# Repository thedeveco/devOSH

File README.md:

# The DevEco Open Hardware Initiative

This repository serves as a central location for open hardware collaboration that is inspired the by devEco.

The hope is create a flourishing hardware ecosystem that the community can rally around, learn from and adapt to create new exciting projects.

## Live stream
- [Live stream informaton](LIVESTREAM.md)

## Directories

### Projects
- [B3VY LED badge](https://github.com/mwelling/b3vy_led)
- [FPV Omnibot](https://github.com/HeavyFalcon678/FPV-Omnibot)
- [Electronic Makerchip](https://github.com/thedeveco/maker-chip-standard)

#### Current Projects
- [ECP-V Wireless](https://github.com/mwelling/ECP-V-Wireless)

### Studies

### Tutorials

## Administrators

### Michael Welling (Discord m_w)

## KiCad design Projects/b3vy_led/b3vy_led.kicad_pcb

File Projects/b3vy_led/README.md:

## B3VY LED badge

A badge design in the shape of the B3VY logo. Created to help promote the B3VY network at Open Sauce Conference 2025.

### Specifications
- ESP32-S3 mini module
- 8x6 grid of programmable RGB LEDs
- USB C connector for power and programming

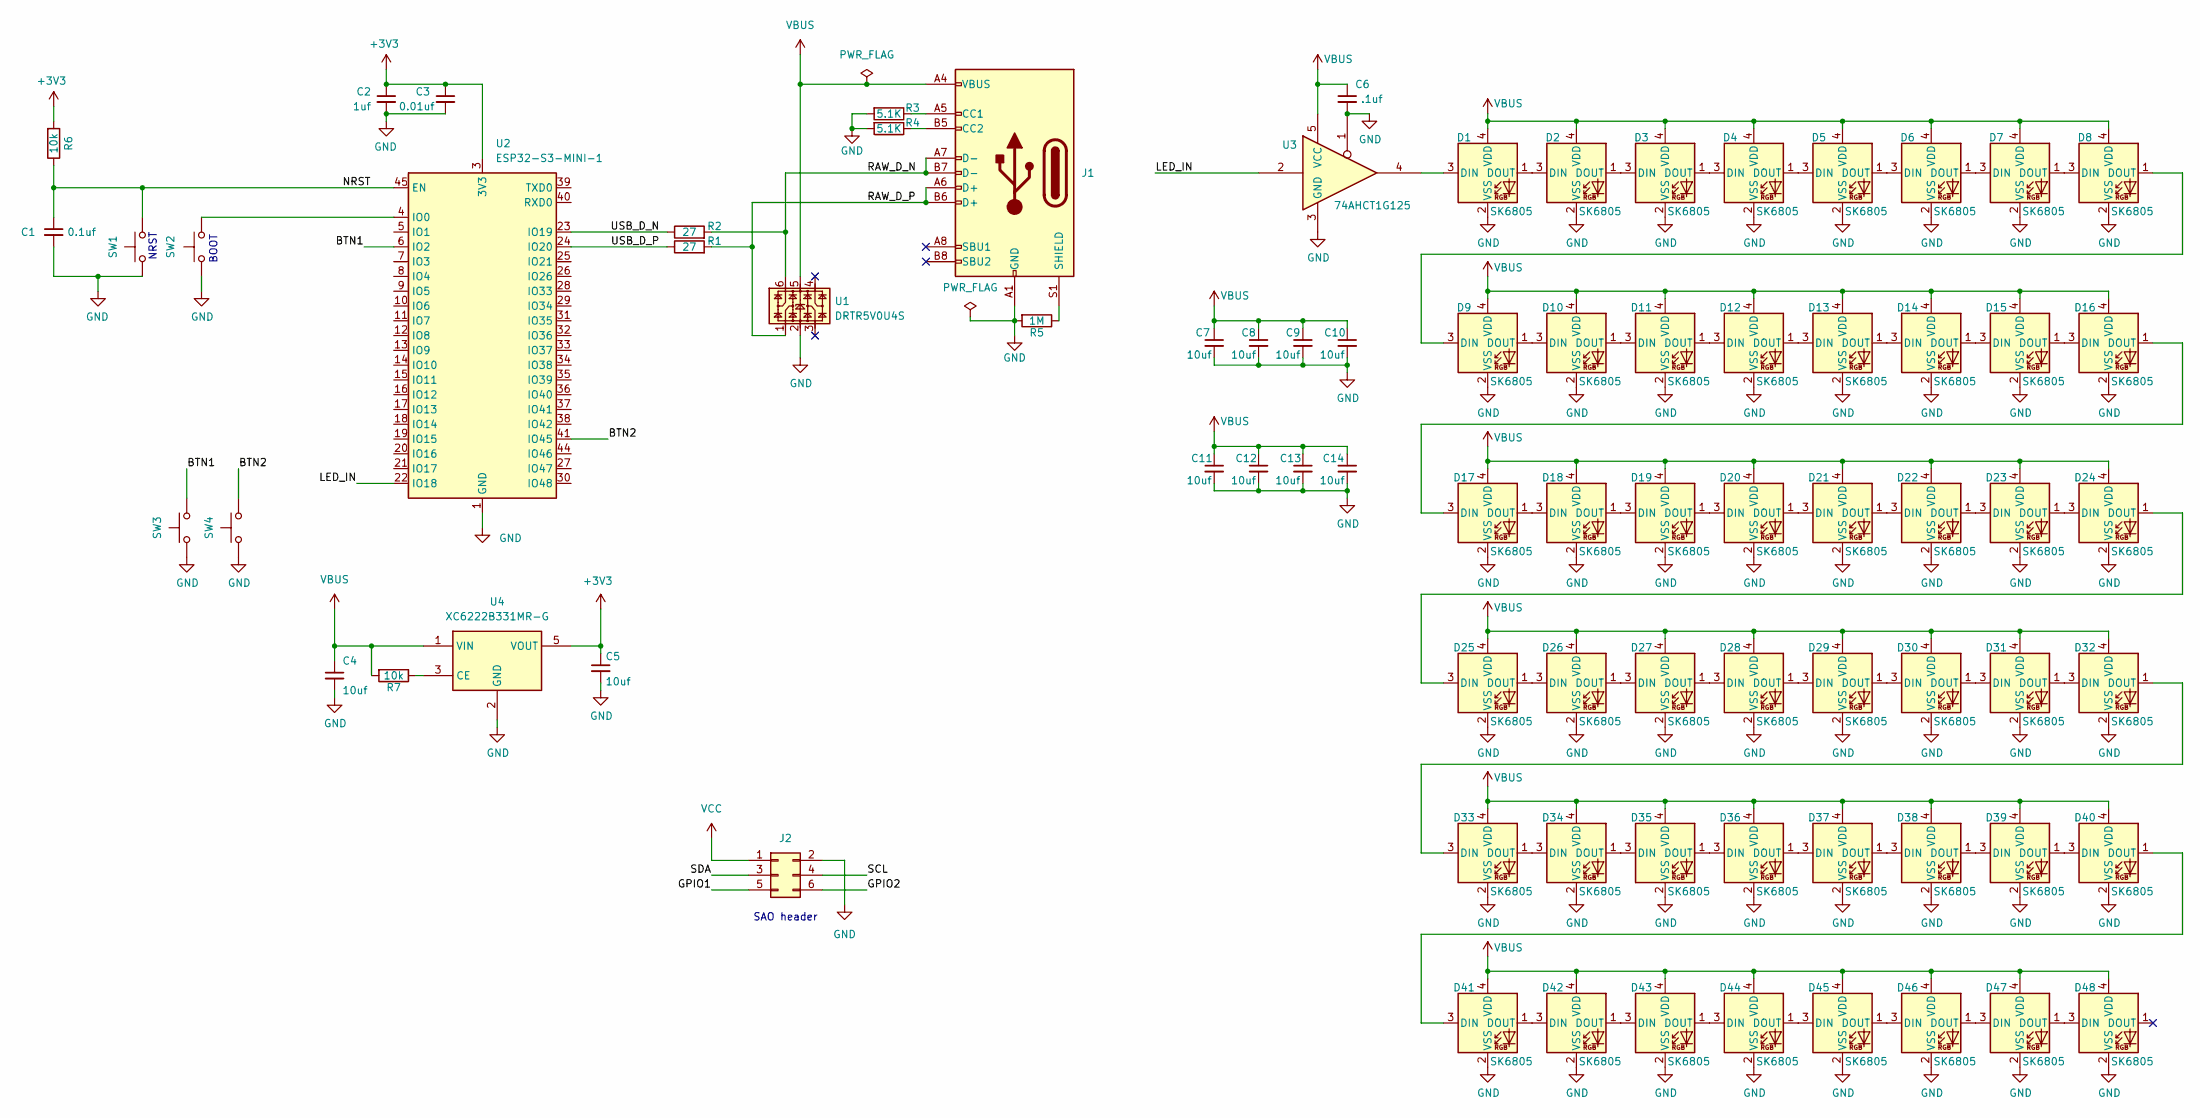
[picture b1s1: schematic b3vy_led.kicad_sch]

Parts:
C1: 0.1uf; C_0402_1005Metric
C2: 1uf; C_0603_1608Metric
C3: 0.01uf; C_0603_1608Metric
C4, C5, C7, C8, C9, C10, C11, C12, C13, C14: 10uf; C_0805_2012Metric
C6: .1uf; C_0603_1608Metric
D1, D2, D3, D4, D5, D6, D7, D8, D9, D10, D11, D12, D13, D14, D15, D16, D17, D18, D19, D20, D21, D22, D23, D24, D25, D26, D27, D28, D29, D30, D31, D32, D33, D34, D35, D36, D37, D38, D39, D40, D41, D42, D43, D44, D45, D46, D47, D48: SK6805; LED_SK6805_PLCC4_2.4x2.7mm_P1.3mm
J1: USB_C_Receptacle_USB2.0; USB_C_Receptacle_HRO_TYPE-C-31-M-12
J2: Conn_02x03_Odd_Even; PinHeader_2x03_P2.54mm_Vertical
R1, R2: 27; R_0402_1005Metric
R3, R4: 5.1K; R_0603_1608Metric
R5: 1M; R_0603_1608Metric
R6, R7: 10k; R_0603_1608Metric
SW1, SW2, SW3, SW4: SW_Push; SW_SPST_PTS810
U1: DRTR5V0U4S; SOT-363_SC-70-6
U2: ESP32-S3-MINI-1; ESP32-S2-MINI-1
U3: 74AHCT1G125; SOT-23-5
U4: XC6222B331MR-G; SOT-23-5

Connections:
+3V3: C2.1, C3.1, C5.1, R6.2, U2.3 (3V3), U4.5 (VOUT)
/BTN1: SW3.2, U2.6 (IO2)
/BTN2: SW4.2, U2.41 (IO45)
/GPIO1: J2.5
/GPIO2: J2.6
/LED_IN: U2.22 (IO18), U3.2
/NRST: C1.1, R6.1, SW1.2, U2.45 (EN)
/RAW_D_N: J1.A7 (D-), J1.B7 (D-), R2.2, U1.6
/RAW_D_P: J1.A6 (D+), J1.B6 (D+), R1.2, U1.1
/SCL: J2.4
/SDA: J2.3
/USB_D_N: R2.1, U2.23 (IO19)
/USB_D_P: R1.1, U2.24 (IO20)
GND: C1.2, C2.2, C3.2, C4.2, C5.2, C6.2, C7.2, C8.2, C9.2, C10.2, C11.2, C12.2, C13.2, C14.2, D1.2 (VSS), D2.2 (VSS), D3.2 (VSS), D4.2 (VSS), D5.2 (VSS), D6.2 (VSS), D7.2 (VSS), D8.2 (VSS), D9.2 (VSS), D10.2 (VSS), D11.2 (VSS), D12.2 (VSS), D13.2 (VSS), D14.2 (VSS), D15.2 (VSS), D16.2 (VSS), D17.2 (VSS), D18.2 (VSS), D19.2 (VSS), D20.2 (VSS), D21.2 (VSS), D22.2 (VSS), D23.2 (VSS), D24.2 (VSS), D25.2 (VSS), D26.2 (VSS), D27.2 (VSS), D28.2 (VSS), D29.2 (VSS), D30.2 (VSS), D31.2 (VSS), D32.2 (VSS), D33.2 (VSS), D34.2 (VSS), D35.2 (VSS), D36.2 (VSS), D37.2 (VSS), D38.2 (VSS), D39.2 (VSS), D40.2 (VSS), D41.2 (VSS), D42.2 (VSS), D43.2 (VSS), D44.2 (VSS), D45.2 (VSS), D46.2 (VSS), D47.2 (VSS), D48.2 (VSS), J1.A1 (GND), J1.A12 (GND), J1.B1 (GND), J1.B12 (GND), J2.2, R3.2, R4.2, R5.2, SW1.1, SW2.1, SW3.1, SW4.1, U1.2, U2.1 (GND), U2.2 (GND), U2.42 (GND), U2.43 (GND), U2.46 (GND), U2.47 (GND), U2.48 (GND), U2.49 (GND), U2.50 (GND), U2.51 (GND), U2.52 (GND), U2.53 (GND), U2.54 (GND), U2.55 (GND), U2.56 (GND), U2.57 (GND), U2.58 (GND), U2.59 (GND), U2.60 (GND), U2.61 (GND), U2.62 (GND), U2.63 (GND), U2.64 (GND), U2.65 (GND), U3.1, U3.3 (GND), U4.2 (GND)
unnamed: D1.3 (DIN), U3.4
unnamed: D1.1 (DOUT), D2.3 (DIN)
unnamed: D2.1 (DOUT), D3.3 (DIN)
unnamed: D3.1 (DOUT), D4.3 (DIN)
unnamed: D4.1 (DOUT), D5.3 (DIN)
unnamed: D5.1 (DOUT), D6.3 (DIN)
unnamed: D6.1 (DOUT), D7.3 (DIN)
unnamed: D7.1 (DOUT), D8.3 (DIN)
unnamed: D8.1 (DOUT), D9.3 (DIN)
unnamed: D9.1 (DOUT), D10.3 (DIN)
unnamed: D10.1 (DOUT), D11.3 (DIN)
unnamed: D11.1 (DOUT), D12.3 (DIN)
unnamed: D12.1 (DOUT), D13.3 (DIN)
unnamed: D13.1 (DOUT), D14.3 (DIN)
unnamed: D14.1 (DOUT), D15.3 (DIN)
unnamed: D15.1 (DOUT), D16.3 (DIN)
unnamed: D16.1 (DOUT), D17.3 (DIN)
unnamed: D17.1 (DOUT), D18.3 (DIN)
unnamed: D18.1 (DOUT), D19.3 (DIN)
unnamed: D19.1 (DOUT), D20.3 (DIN)
unnamed: D20.1 (DOUT), D21.3 (DIN)
unnamed: D21.1 (DOUT), D22.3 (DIN)
unnamed: D22.1 (DOUT), D23.3 (DIN)
unnamed: D23.1 (DOUT), D24.3 (DIN)
unnamed: D24.1 (DOUT), D25.3 (DIN)
unnamed: D25.1 (DOUT), D26.3 (DIN)
unnamed: D26.1 (DOUT), D27.3 (DIN)
unnamed: D27.1 (DOUT), D28.3 (DIN)
unnamed: D28.1 (DOUT), D29.3 (DIN)
unnamed: D29.1 (DOUT), D30.3 (DIN)
unnamed: D30.1 (DOUT), D31.3 (DIN)
unnamed: D31.1 (DOUT), D32.3 (DIN)
unnamed: D32.1 (DOUT), D33.3 (DIN)
unnamed: D33.1 (DOUT), D34.3 (DIN)
unnamed: D34.1 (DOUT), D35.3 (DIN)
unnamed: D35.1 (DOUT), D36.3 (DIN)
unnamed: D36.1 (DOUT), D37.3 (DIN)
unnamed: D37.1 (DOUT), D38.3 (DIN)
unnamed: D38.1 (DOUT), D39.3 (DIN)
unnamed: D39.1 (DOUT), D40.3 (DIN)
unnamed: D40.1 (DOUT), D41.3 (DIN)
unnamed: D41.1 (DOUT), D42.3 (DIN)
unnamed: D42.1 (DOUT), D43.3 (DIN)
unnamed: D43.1 (DOUT), D44.3 (DIN)
unnamed: D44.1 (DOUT), D45.3 (DIN)
unnamed: D45.1 (DOUT), D46.3 (DIN)
unnamed: D46.1 (DOUT), D47.3 (DIN)
unnamed: D47.1 (DOUT), D48.3 (DIN)
unnamed: J1.A5 (CC1), R3.1
unnamed: J1.B5 (CC2), R4.1
unnamed: J1.S1 (SHIELD), R5.1
unnamed: SW2.2, U2.4 (IO0)
unnamed: R7.1, U4.3 (CE)
VBUS: C4.1, C6.1, C7.1, C8.1, C9.1, C10.1, C11.1, C12.1, C13.1, C14.1, D1.4 (VDD), D2.4 (VDD), D3.4 (VDD), D4.4 (VDD), D5.4 (VDD), D6.4 (VDD), D7.4 (VDD), D8.4 (VDD), D9.4 (VDD), D10.4 (VDD), D11.4 (VDD), D12.4 (VDD), D13.4 (VDD), D14.4 (VDD), D15.4 (VDD), D16.4 (VDD), D17.4 (VDD), D18.4 (VDD), D19.4 (VDD), D20.4 (VDD), D21.4 (VDD), D22.4 (VDD), D23.4 (VDD), D24.4 (VDD), D25.4 (VDD), D26.4 (VDD), D27.4 (VDD), D28.4 (VDD), D29.4 (VDD), D30.4 (VDD), D31.4 (VDD), D32.4 (VDD), D33.4 (VDD), D34.4 (VDD), D35.4 (VDD), D36.4 (VDD), D37.4 (VDD), D38.4 (VDD), D39.4 (VDD), D40.4 (VDD), D41.4 (VDD), D42.4 (VDD), D43.4 (VDD), D44.4 (VDD), D45.4 (VDD), D46.4 (VDD), D47.4 (VDD), D48.4 (VDD), J1.A4 (VBUS), J1.A9 (VBUS), J1.B4 (VBUS), J1.B9 (VBUS), R7.2, U1.5, U3.5 (VCC), U4.1 (VIN)
VCC: J2.1

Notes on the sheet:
NRST
BOOT
SAO header

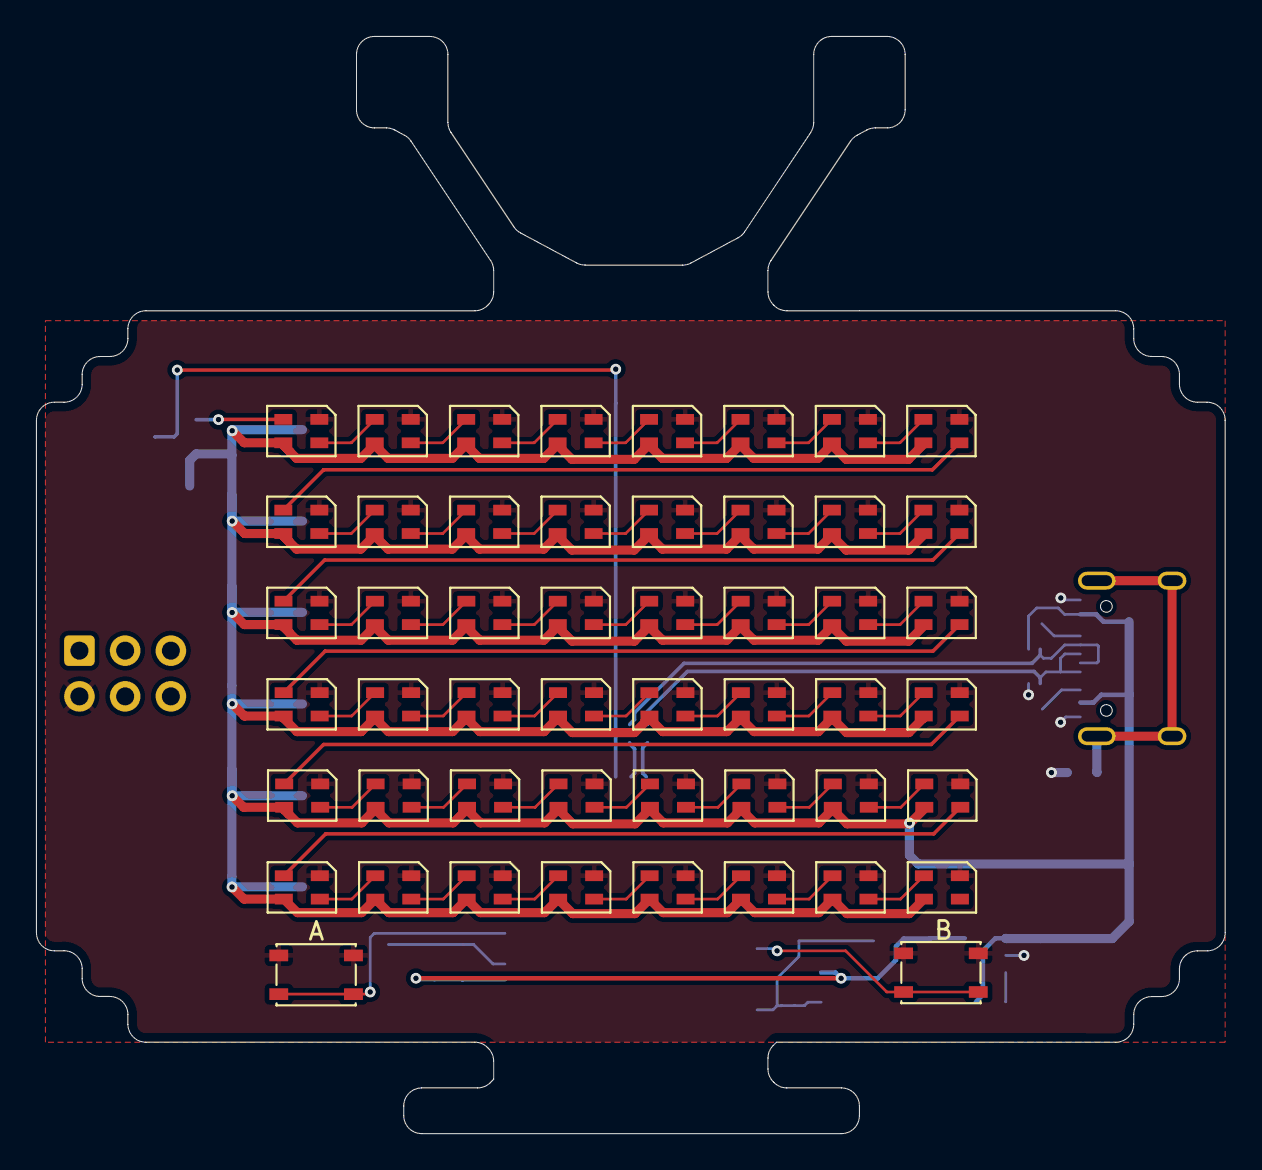
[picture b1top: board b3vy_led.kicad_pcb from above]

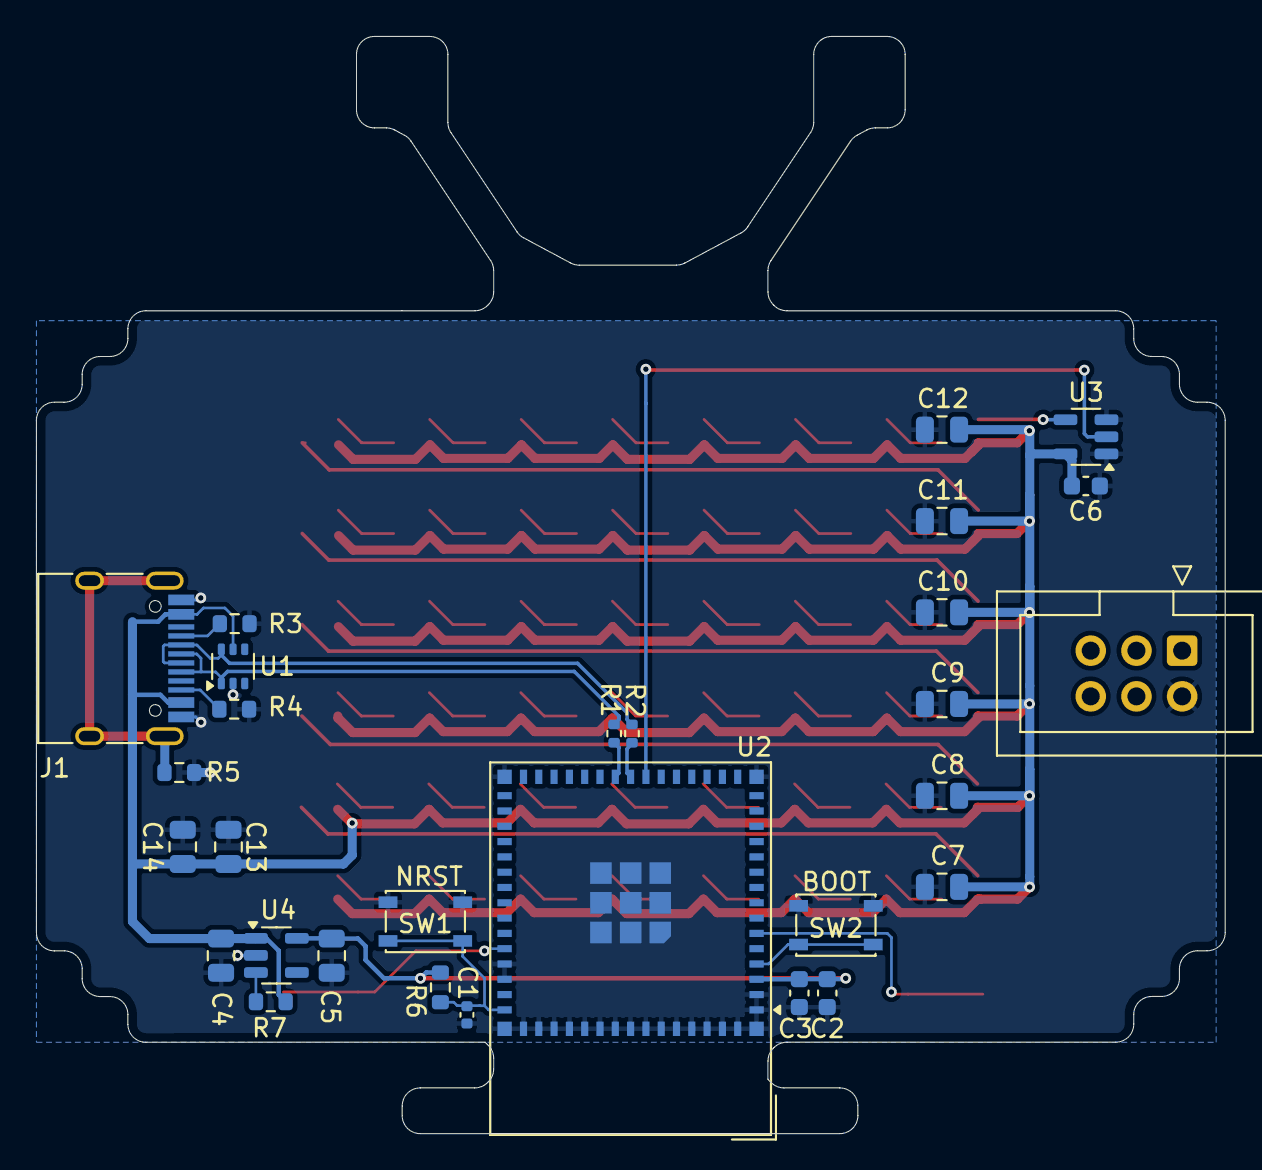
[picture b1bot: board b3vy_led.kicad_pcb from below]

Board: 2 copper layers, 66.0 x 61.0 mm, 79 parts (29 on the bottom side), 64 nets.

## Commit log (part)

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2024-11-21 Create README.md
    Created the README.md file
2024-11-21 Added Administrators to heading
2024-11-21 Adding CONTRIBUTE.md - needs editing to work with the Open Hardware Initiative.
    Adding CONTRIBUTE.md - needs more editing for the Open Hardware Initiative.
    Taken from the 96boards project.
2024-11-23 Initializing KiCad project for the Robot Smart Home Controller
2024-11-23 First attempt
2024-11-23 I decided it would be better to organize everything by Project Name
2024-11-23 New schematic
2024-11-23 Removed old files
2024-11-23 Added discord nicks
2024-11-23 Updated REAME
2024-11-23 Added README for Robot Smart Home Controller
2024-11-23 Removing old files
2024-11-23 Added new files
2024-11-23 Added a short description of the Robot Smart Home Controller
2024-11-24 Adding the Projects and Tutorials directories
2024-11-24 Updating
2024-11-24 Adding the Studies directory
2024-11-24 Moving the Robot_Smart_Home_Controller into Projects
2024-11-24 Updated top README to include the directories we have
2024-11-24 Added LICENSE.md
2024-11-24 Added docs directory from PortalNetwork
2024-11-24 Removed CONTRIBUE.md
2024-11-25 Moved the Robot Smart Home Controller to the Studies directory
2024-11-25 Added new backups
2024-11-25 Removed backups.
2024-11-28 Adding updated schematic - switches and resistors added.
2024-11-28 Renaming docs to DevEco
2024-11-28 Renamed DevEco to devDocs
2024-11-28 Adding Contributed/docs
2024-11-28 Adjusted the Contributed/READ.md
2024-11-28 Added docs/README.md
2024-11-29 Edits to CONTRIBUTING.md
2024-11-29 Updated CONTRIBUTING.md to apply to devHW. Not done yet!
2024-11-29 Added the git remote add step
2024-12-01 Moving CODE_OF_CONDUCT.md, CONTRIBUTING.md, and FAQ.md back to the repo root.
2024-12-01 Updated schematic for Robot Smart Home Controller
2024-12-01 Creating .gitignore to ignore Robot Smart Home Controller KiCad backup dir
2024-12-02 Changed a reference to the Portal Network to Open Hardware Initiative.
2024-12-07 Update CONTRIBUTING.md
    Remove references to portal network and switch "Open Hardware Initiative".
2025-06-19 Initial commit of the B3VY LED badge
2025-06-21 Update board outline and add SAO header
    TODO: figure out how to power from SAO or add battery.
2025-06-30 Update to sane LED ordering
2025-06-30 Rename folder with legit name
2025-06-30 Rename files with legit name
2025-09-27 Remove abandoned contribs and admin
2025-09-27 Add README to B3VY LED project
2026-02-22 Add electronic makerchip kicad project
2026-02-22 Add gitignore and delete backups
2026-02-24 Add new makerchip repo as a submodule
2026-02-26 Moving emakerchip kicad files to other repo
2026-02-26 Update submodule pin for makerchip project
2026-02-26 Add link to new makerchip project
2026-03-31 Add live stream information to README
    Added live stream schedule and links to README.
2026-04-01 Remove live stream details from README
    Removed live stream information and links from README.
2026-04-01 Add a markdown page specifically stream docs
2026-04-01 Fix stream recording link
    Updated the stream recording link to use an embedded thumbnail.
2026-04-01 Add submodule link for fpv-omnibot
2026-04-01 Add FPV Omnibot project link to README
2026-04-01 Update module pin for makerchip repo
2026-04-04 Update LIVESTREAM.md with new links and agenda
    Added links to resources and updated agenda for April 7th.
2026-04-04 Enhance LIVESTREAM.md with links and new agenda
    Updated previous streams section with links and corrected typos.
2026-04-13 Update LIVESTREAM.md to reflect schedule changes
2026-04-15 Move B3vy LED project to submodule
2026-04-15 Update B3VY LED badge link
2026-04-15 Update LIVESTREAM.md with April 14th details
    Added details for the April 14th 2026 stream and updated previous streams section.
2026-04-29 Revise LIVESTREAM.md with new dates and links
    Updated stream schedule and added previous stream details.
2026-05-06 Update LIVESTREAM.md with new agenda and details
    Added agenda for the upcoming stream on May 12th 2026 and updated previous streams section.
2026-05-06 Update submodules
2026-05-12 Update Twitch link and agenda for May 12th stream
    Updated Twitch stream link and modified agenda for the upcoming stream.
2026-05-13 Update LIVESTREAM.md with new agenda and updates
    Added agenda for May 19th 2026 and updated previous streams.
2026-05-13 Update live stream time to 7:30pm CDT
2026-05-19 Update agenda for May 19th 2026 livestream
2026-05-20 Revise live stream schedule and agenda
    Updated stream schedule and added agenda for May 26th 2026.
2026-05-20 Update submodule for FPV-omnibot
2026-05-27 Change stream date to June 2nd 2026
    Updated stream date and added details for previous streams.
2026-06-09 Change stream date to June 9th 2026 with agenda
    Updated the date and agenda for the upcoming stream.
2026-06-10 Update LIVESTREAM.md with new agenda and stream details
    Added agenda for June 16th stream and updated previous streams section.
2026-06-10 Add stream recording link for June 9th 2026
2026-06-17 Update LIVESTREAM.md with new stream details
    Added details about the June 16th stream and previous streams.
2026-06-22 Update submodule for makerchip
2026-06-23 Update LIVESTREAM.md with June 23rd agenda
    Added agenda for the upcoming June 23rd stream.
